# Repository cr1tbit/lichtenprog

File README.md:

## Lichtenprog - an rather-cheap-USB-to-UART-bridge-with-3v3-out

### Raison d'etre

The device is based on CP2102n - meaning it should work properly on any OS without messy drivers from unknown sources. It's also cheaper than legit FT232 chips.

Why can't I power my stuff from basic USB-to-UART bridges? Some of those serial adapters out there have basic 3.3V-out bulitin, coming usually from main IC's LDO output. Being able to supply like 100 miliamps. I want my full 500mA from the USB! Seriously, throwing that external LDO costs like 10 cents.

I also added an simple circut for estimating the connected device's current draw. You may left it unpopulated, to save like another 70c.

Honestly, I've found myself using this board to supply my 3v3 devices from wallplugs, it's just convenient to have like 10 of those.

## Customizing your Lichtenprog

After soldering your device, you may want to reprogram the CP2102n a little bit, in order to set:
 * TX/RX leds functionality (by default disabled)
 * Max current draw USB descriptor
 * Your custom name and manufacturer name (yay!)

Please, just do not modify PID and VID, or els you risk effectively bricking your brand new 3$ device.

To modify these values, you may use official "xpressconfigurator" from SiLabs

I couldn't make this tool to work on linux though - take a look at this CLI-based project, which should allow setting up basic stuff.

https://github.com/cr1tbit/cp210x-cfg

## Photo (outdated)

## License
The hardware design files, including schematics and PCB layout, are licensed under the CERN Open Hardware Licence v2 CERN-OHL-P.

All documentation is released under CC BY-SA 4.0

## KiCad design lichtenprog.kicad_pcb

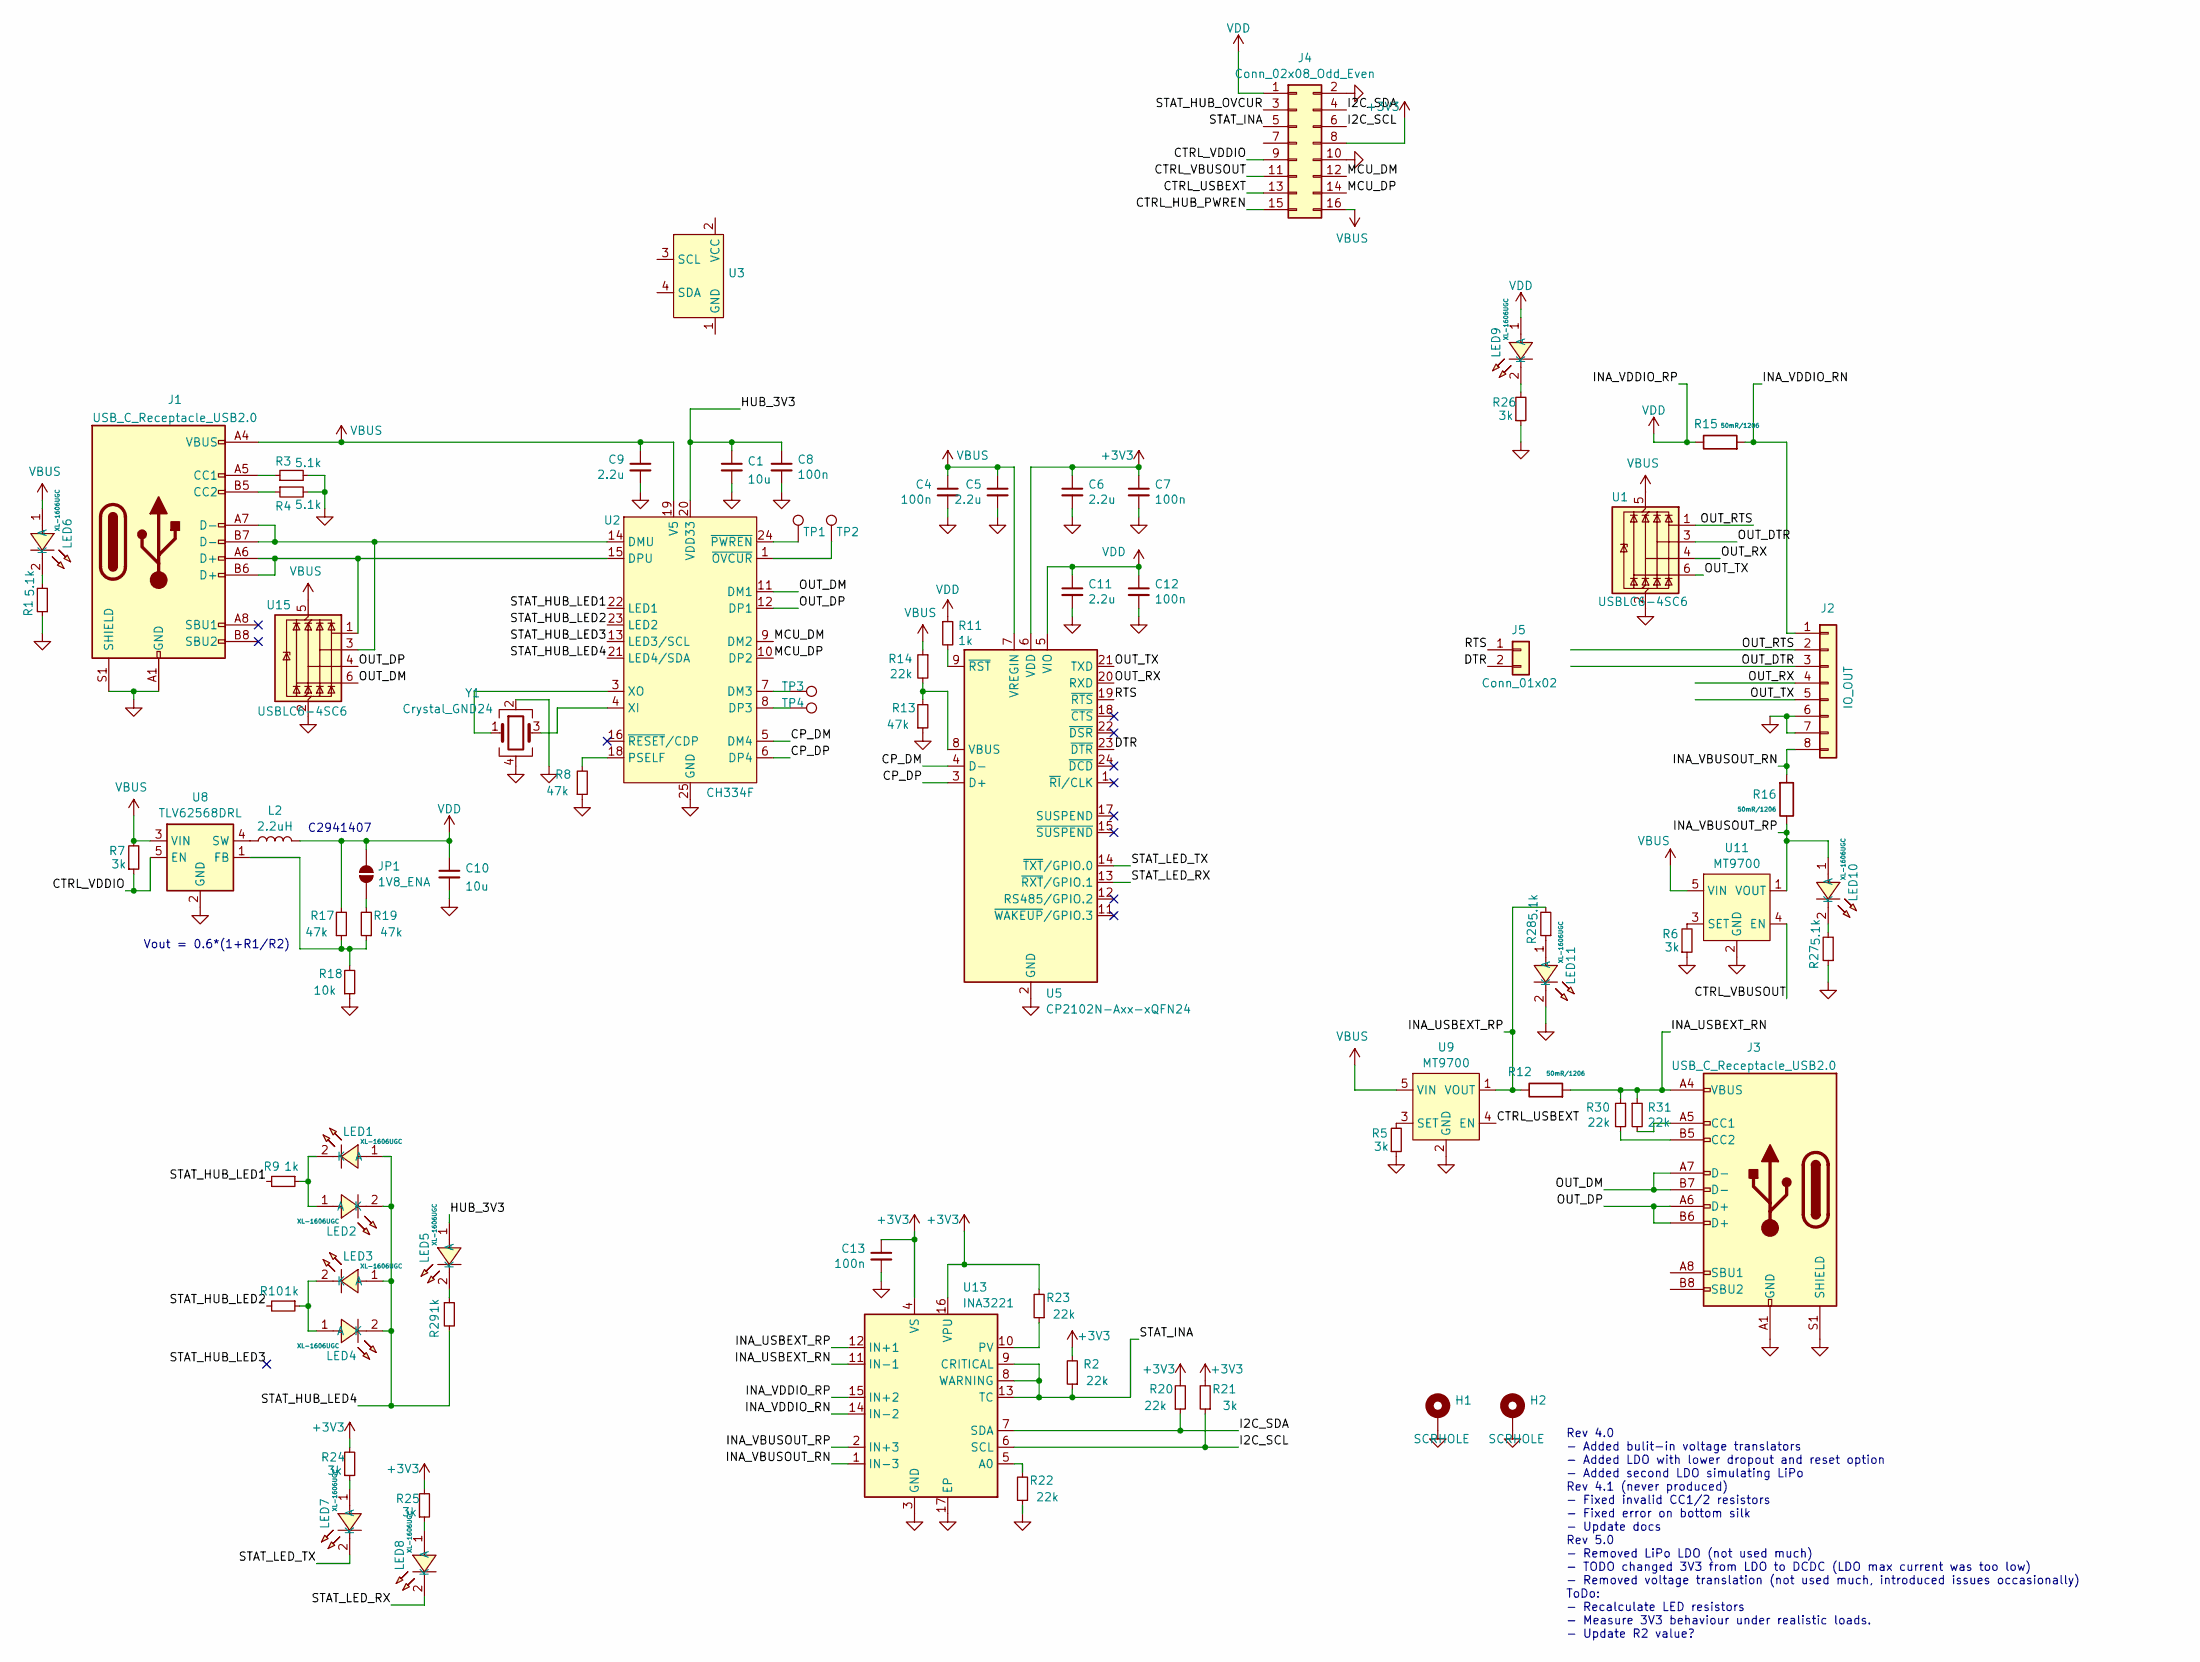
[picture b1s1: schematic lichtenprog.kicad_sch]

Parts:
C1, C10: 10u; C_0603_1608Metric; LCSC C19702
C4, C7, C8, C12, C13: 100n; C_0402_1005Metric; LCSC C1525
C5, C6, C9, C11: 2.2u; C_0603_1608Metric; LCSC C12530
H1, H2: SCRHOLE; MountingHole_2.2mm_M2_ISO7380_Pad
J1, J3: USB_C_Receptacle_USB2.0; USB_C_Receptacle_HRO_TYPE-C-31-M-12; LCSC C165948
J2: IO_OUT; PinHeader_1x08_P2.54mm_Vertical; LCSC C0000
J4: Conn_02x08_Odd_Even; PinSocket_2x08_P1.27mm_Vertical_SMD
J5: Conn_01x02; PinHeader_1x02_P2.54mm_Vertical
JP1: 1V8_ENA; SolderJumper-2_P1.3mm_Open_RoundedPad1.0x1.5mm
L2: 2.2uH; L_Sunlord_MWSA0412S
LED1, LED2, LED3, LED4, LED5, LED6, LED7, LED8, LED9, LED10, LED11: XL-1606UGC; LED-SMD_L1.7-W1.1-R-RD_GREEN; LCSC Part C965863
R1, R3, R4, R27, R28: 5.1k; R_0402_1005Metric; LCSC C25117
R2, R14, R20, R22, R23, R30, R31: 22k; R_0402_1005Metric; LCSC C25768
R5, R6, R7, R21, R24, R25, R26: 3k; R_0402_1005Metric; LCSC C25768
R8, R13: 47k; R_0402_1005Metric; LCSC C25792
R9, R10, R29: 1k; R_0402_1005Metric; LCSC C25768
R11: 1k; R_0402_1005Metric; LCSC C11702
R12, R15, R16: 50mR/1206; R_1206_3216Metric_Pad1.30x1.75mm_HandSolder; LCSC C601102
R17, R19: 47k; R_0402_1005Metric; LCSC C25768
R18: 10k; R_0402_1005Metric; LCSC C25792
TP1, TP2, TP3, TP4: TestPoint; TestPoint_Pad_D1.0mm
U1, U15: USBLC6-4SC6; SOT-23-6
U2: CH334F; QFN-24_L4.0-W4.0-P0.50-BL-EP2.8; LCSC Part C5187527
U3: OLED_4Pin_128x64_new
U5: CP2102N-Axx-xQFN24; QFN-24-1EP_4x4mm_P0.5mm_EP2.6x2.6mm
U8: TLV62568DRL; SOT-563
U9, U11: MT9700; SOT-23-5_L3.0-W1.7-P0.95-LS2.8-BR; LCSC Part C89855
U13: INA3221; Texas_RGV0016A_VQFN-16-1EP_4x4mm_P0.65mm_EP2.1x2.1mm
Y1: Crystal_GND24; Crystal_SMD_3225-4Pin_3.2x2.5mm

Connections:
+3V3: C6.1, C7.1, C13.1, J4.8, R2.2, R20.2, R21.2, R23.2, R24.2, R25.2, U5.6 (VDD), U13.4 (VS), U13.16 (VPU)
/CP_DM: U2.5 (DM4), U5.4 (D-)
/CP_DP: U2.6 (DP4), U5.3 (D+)
/CTRL_HUB_PWREN: J4.15
/CTRL_USBEXT: J4.13, U9.4 (EN)
/CTRL_VBUSOUT: J4.11, U11.4 (EN)
/CTRL_VDDIO: J4.9, R7.1, U8.5 (EN)
/DTR: J5.2, U5.23 (~DTR)
/HUB_3V3: C1.1, C8.1, LED5.1 (A), U2.20 (VDD33)
/I2C_SCL: J4.6, R21.1, U13.6 (SCL)
/I2C_SDA: J4.4, R20.1, U13.7 (SDA)
/INA_USBEXT_RN: J3.A4 (VBUS), J3.A9 (VBUS), J3.B4 (VBUS), J3.B9 (VBUS), R12.2, R30.1, R31.1, U13.11 (IN-1)
/INA_USBEXT_RP: R12.1, R28.2, U9.1 (VOUT), U13.12 (IN+1)
/INA_VBUSOUT_RN: J2.8, R16.2, U13.1 (IN-3)
/INA_VBUSOUT_RP: LED10.1 (A), R16.1, U11.1 (VOUT), U13.2 (IN+3)
/INA_VDDIO_RN: J2.1, R15.2, U13.14 (IN-2)
/MCU_DM: J4.12, U2.9 (DM2)
/MCU_DP: J4.14, U2.10 (DP2)
/OUT_DM: J3.A7 (D-), J3.B7 (D-), U2.11 (DM1), U15.6 (I/O4)
/OUT_DP: J3.A6 (D+), J3.B6 (D+), U2.12 (DP1), U15.4 (I/O3)
/OUT_DTR: J2.3, U1.3 (I/O2)
/OUT_RTS: J2.2, U1.1 (I/O1)
/OUT_RX: J2.4, U1.4 (I/O3), U5.20 (RXD)
/OUT_TX: J2.5, U1.6 (I/O4), U5.21 (TXD)
/RTS: J5.1, U5.19 (~RTS)
/STAT_HUB_LED1: R9.2, U2.22 (LED1)
/STAT_HUB_LED2: R10.2, U2.23 (LED2)
/STAT_HUB_LED3: U2.13 (LED3/SCL)
/STAT_HUB_LED4: LED1.1 (A), LED2.2 (K), LED3.1 (A), LED4.2 (K), R29.2, U2.21 (LED4/SDA)
/STAT_HUB_OVCUR: J4.3
/STAT_INA: J4.5, R2.1, U13.8 (WARNING), U13.9 (CRITICAL), U13.13 (TC)
/STAT_LED_RX: LED8.2 (K), U5.13 (~RXT/GPIO.1)
/STAT_LED_TX: LED7.2 (K), U5.14 (~TXT/GPIO.0)
GND: C1.2, C4.2, C5.2, C6.2, C7.2, C8.2, C9.2, C10.2, C11.2, C12.2, C13.2, H1.1, H2.1, J1.A1 (GND), J1.A12 (GND), J1.B1 (GND), J1.B12 (GND), J1.S1 (SHIELD), J2.6, J2.7, J3.A1 (GND), J3.A12 (GND), J3.B1 (GND), J3.B12 (GND), J3.S1 (SHIELD), J4.2, J4.10, LED11.2 (K), R1.1, R3.2, R4.2, R5.1, R6.1, R8.1, R13.1, R18.1, R22.1, R26.1, R27.1, U1.2 (GND), U2.25 (GND), U5.2 (GND), U5.25 (GND), U8.2 (GND), U9.2 (GND), U11.2 (GND), U13.3 (GND), U13.17 (EP), U15.2 (GND), Y1.2, Y1.4
unnamed: J1.A5 (CC1), R3.1
unnamed: J1.B5 (CC2), R4.1
unnamed: J3.A5 (CC1), R31.2
unnamed: J3.B5 (CC2), R30.2
unnamed: JP1.1 (A), R19.2
unnamed: LED1.2 (K), LED2.1 (A), R9.1
unnamed: LED3.2 (K), LED4.1 (A), R10.1
unnamed: LED5.2 (K), R29.1
unnamed: LED6.2 (K), R1.2
unnamed: LED7.1 (A), R24.1
unnamed: LED8.1 (A), R25.1
unnamed: LED9.2 (K), R26.2
unnamed: LED10.2 (K), R27.2
unnamed: LED11.1 (A), R28.1
unnamed: TP3.1, U2.7 (DM3)
unnamed: TP4.1, U2.8 (DP3)
unnamed: R8.2, U2.18 (PSELF)
unnamed: U2.4 (XI), Y1.3
unnamed: U2.3 (XO), Y1.1
unnamed: TP2.1, U2.1 (~OVCUR)
unnamed: TP1.1, U2.24 (~PWREN)
unnamed: R13.2, R14.2, U5.8 (VBUS)
unnamed: R11.2, U5.9 (~RST)
unnamed: R17.1, R18.2, R19.1, U8.1 (FB)
unnamed: L2.1, U8.4 (SW)
unnamed: R5.2, U9.3 (SET)
unnamed: R6.2, U11.3 (SET)
unnamed: R22.2, U13.5 (A0)
unnamed: R23.1, U13.10 (PV)
unnamed: J1.A6 (D+), J1.B6 (D+), U2.15 (DPU), U15.1 (I/O1)
unnamed: J1.A7 (D-), J1.B7 (D-), U2.14 (DMU), U15.3 (I/O2)
VBUS: C4.1, C5.1, C9.1, J1.A4 (VBUS), J1.A9 (VBUS), J1.B4 (VBUS), J1.B9 (VBUS), J4.16, LED6.1 (A), R7.2, R14.1, U1.5 (VBUS), U2.19 (V5), U5.7 (VREGIN), U8.3 (VIN), U9.5 (VIN), U11.5 (VIN), U15.5 (VBUS)
VDD: C10.1, C11.1, C12.1, J4.1, JP1.2 (B), L2.2, LED9.1 (A), R11.1, R15.1, R17.2, U5.5 (VIO), U13.15 (IN+2)

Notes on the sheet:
C2941407
Vout = 0.6*(1+R1/R2)
Rev 4.0 - Added bulit-in voltage translators - Added LDO with lower dropout and reset option - Added second LDO simulating LiPo Rev 4.1 (never produced) - Fixed invalid CC1/2 resistors - Fixed error on bottom silk - Update docs Rev 5.0 - Removed LiPo LDO (not used much) - TODO changed 3V3 from LDO 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

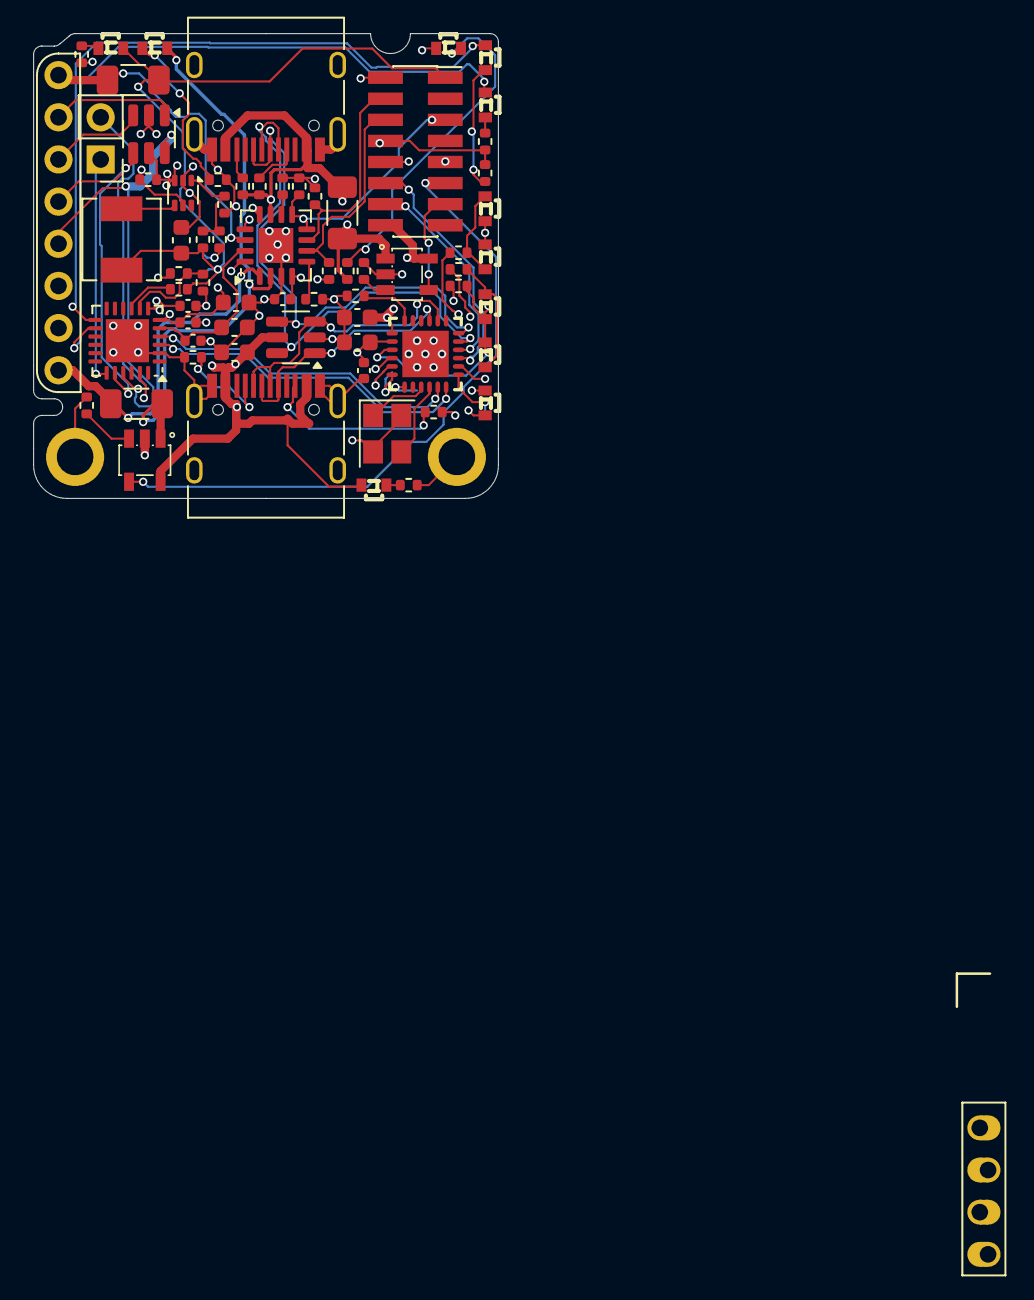
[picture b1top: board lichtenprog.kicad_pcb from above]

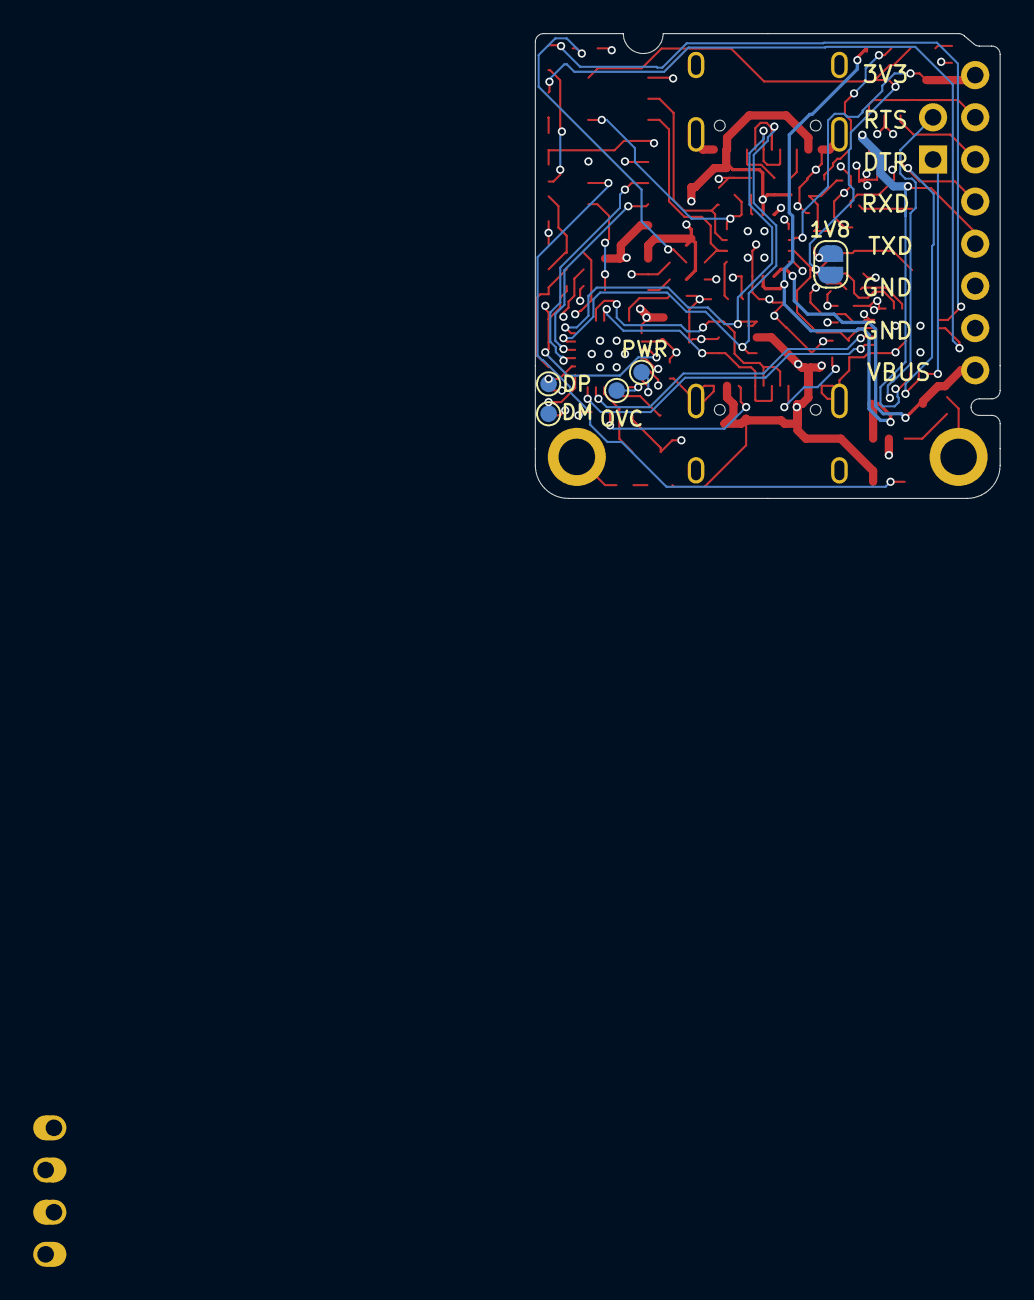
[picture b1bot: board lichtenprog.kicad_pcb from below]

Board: 4 copper layers, 28.0 x 28.0 mm, 76 parts (5 on the bottom side), 64 nets.

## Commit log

2020-02-06 1st rev
2020-02-06 adjusting BOM and cpl for production
2020-05-19 1st rev. 3d model
2020-05-19 rev 2 schematic and PCB do-over
2020-05-19 repo cleanup
2020-05-22 finishing PCB, adding description
2020-05-31 finishing readme
2020-05-31 fab outputs for rev 2.0
2020-08-08 adding photo
2020-08-08 Adding image to readme
2022-04-15 changing pc
2022-09-15 some PCB swag, preparing JLC BOM
2024-06-02 repo cleanup before next rev
2024-06-02 set proper license, some cleanup
2024-07-21 route complt
